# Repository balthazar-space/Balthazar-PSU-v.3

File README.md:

# Balthazar

Open-hardware laptop computer modules description and concept.

These are electronic schematic modules as presented at https://balthazar.space/wiki/Balthazar with the main aim for team access. See the [main repository](https://github.com/balthazar-space/balthazar) for other designs.

# Balthazar PSU v.3 

Module BalthazarPSU3 is a combined 1S battery charger, buck-boost converter to 5V, boost converter to 12V and stereo power amplifier. 

KiCad 6.99 files.

## License

All resources except the keyboard firmware - which is licensed with with GPLv3 or later - licensed under the CERN Open Hardware Licence CERN-OHL W V.2.0

Version 2.0 of the CERN-OHL introduces three variants of the licence – strongly (S) reciprocal, weakly (W) reciprocal and permissive (P) – which aim to address specific constraints caused by different collaboration models currently used in open-hardware projects. 

The first two variants mean that if any product is made using an open hardware design, the design of that product, including any improvements or modifications, should be made available under the same licence as that of the original product. Permissive licences do not impose this condition.

See the [LICENSE.md](./LICENSE.md) file for more information.

## Funding

This project is funded through the [NGI Zero Entrust Fund](https://nlnet.nl/entrust), a fund
established by [NLnet](https://nlnet.nl) with financial support from the European Commission's
[Next Generation Internet](https://ngi.eu) program. Learn more on the [NLnet project page](https://nlnet.nl/project/Balthazar-Casing/).

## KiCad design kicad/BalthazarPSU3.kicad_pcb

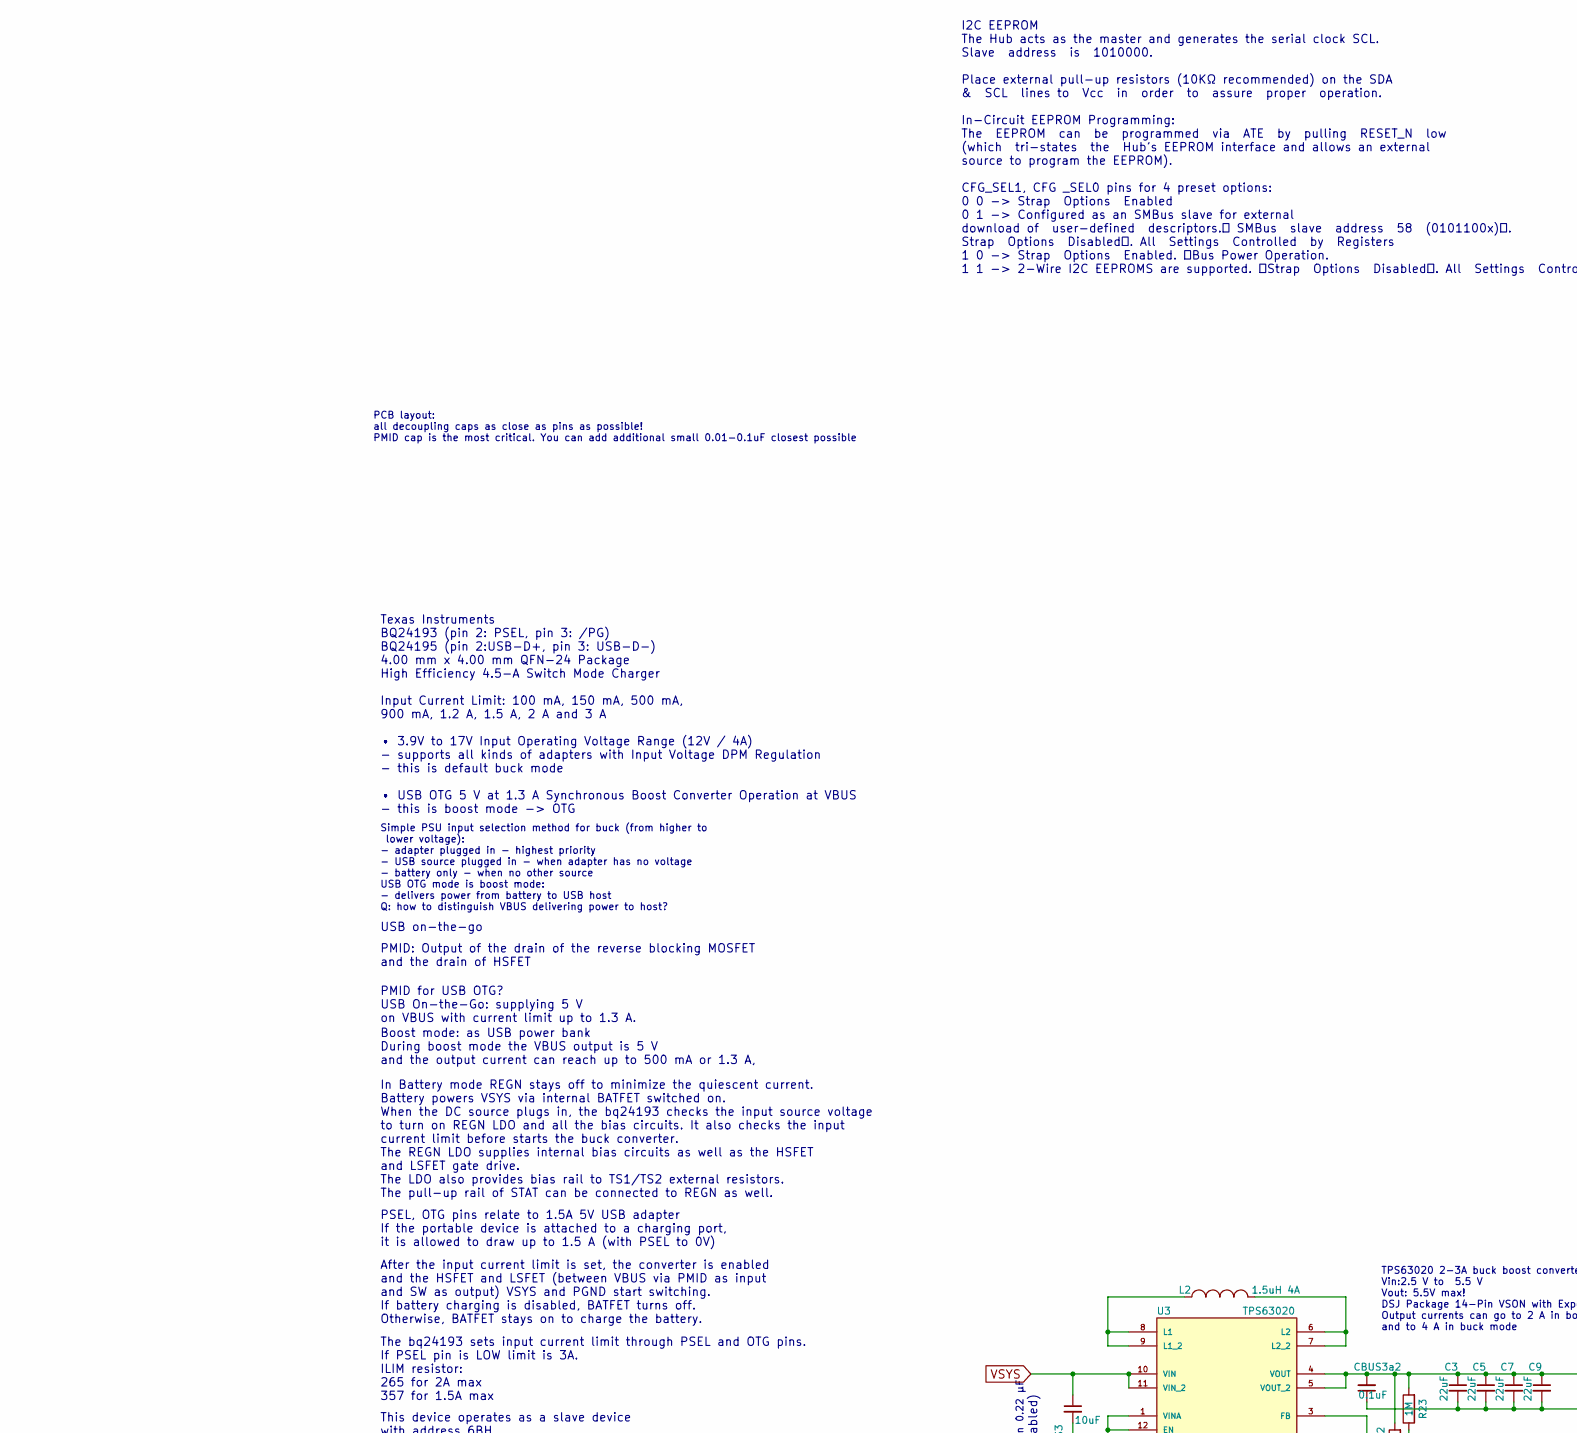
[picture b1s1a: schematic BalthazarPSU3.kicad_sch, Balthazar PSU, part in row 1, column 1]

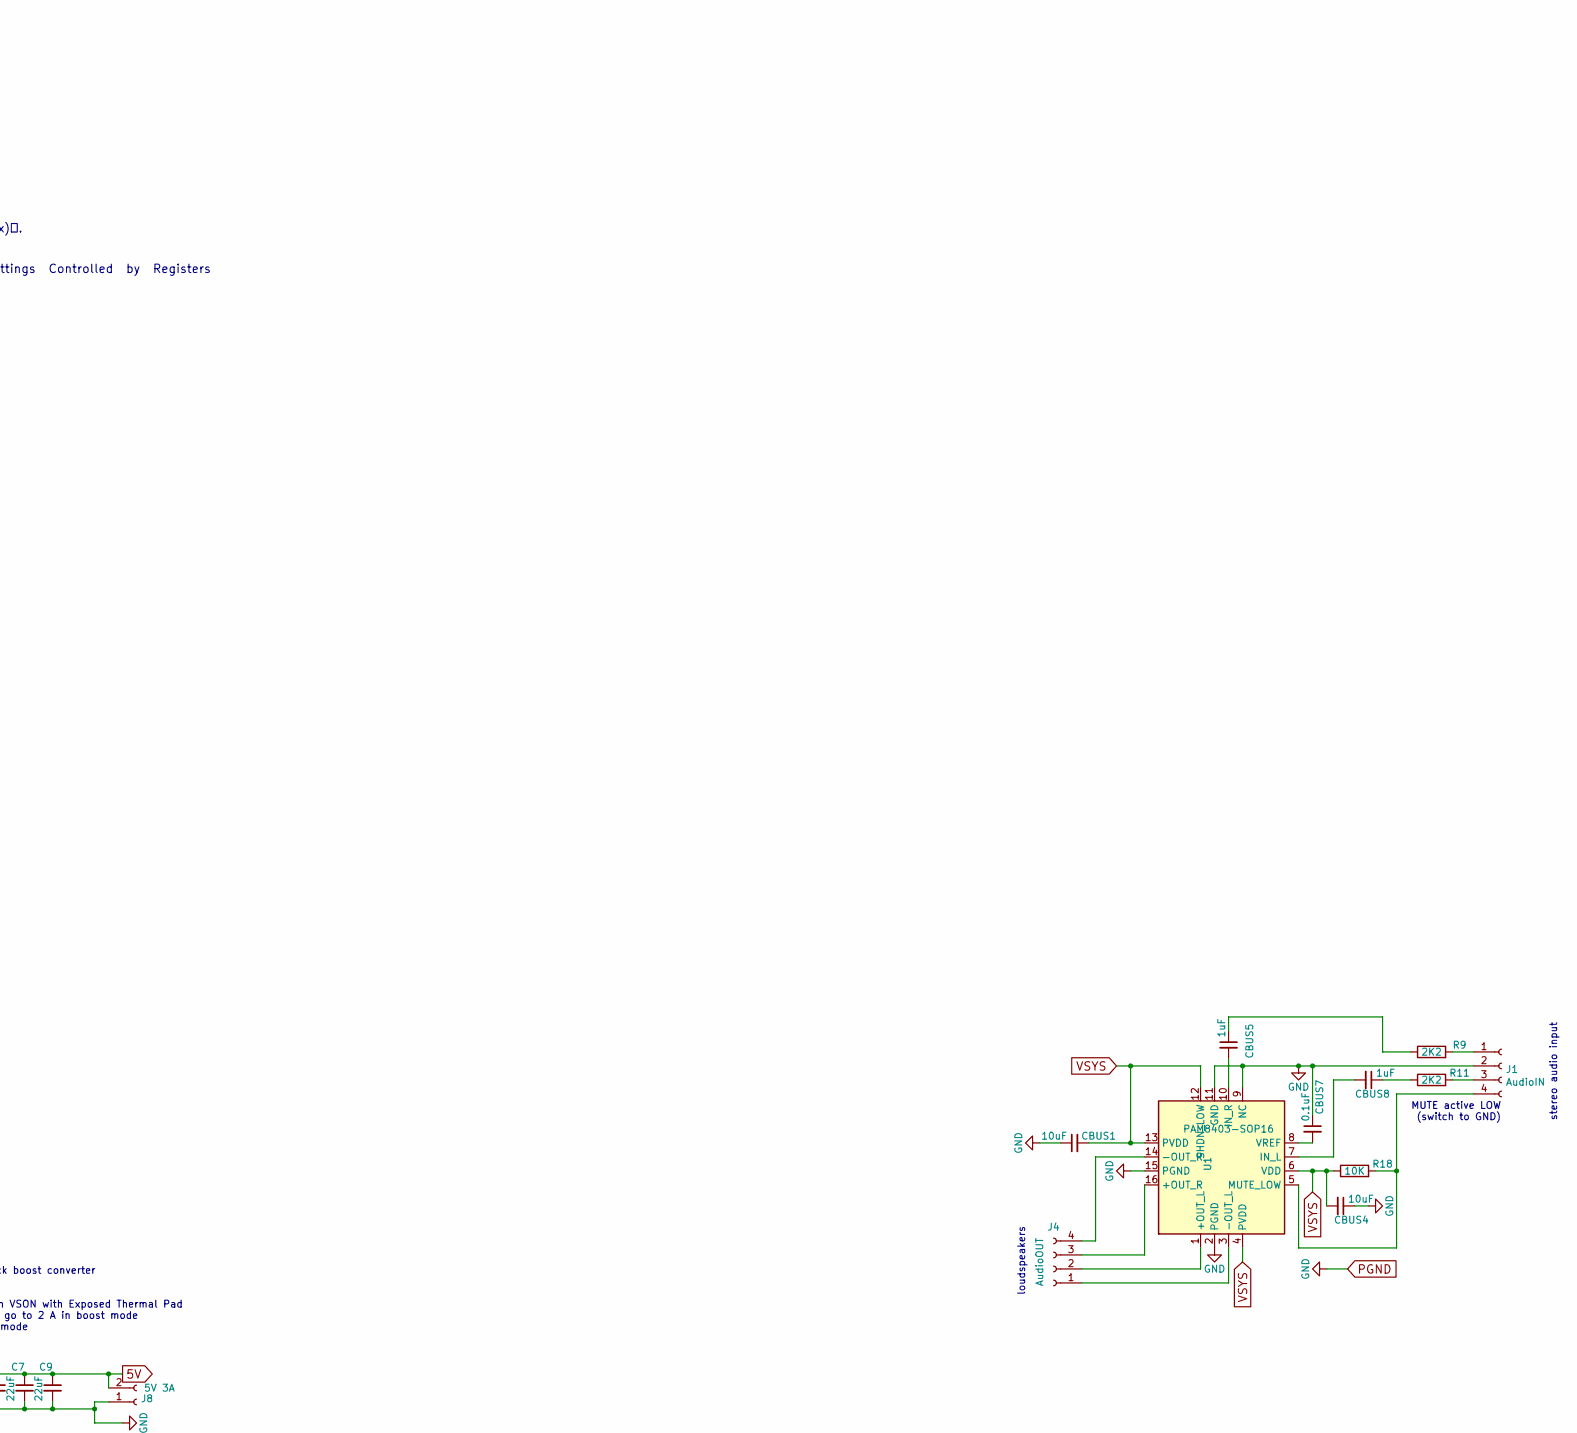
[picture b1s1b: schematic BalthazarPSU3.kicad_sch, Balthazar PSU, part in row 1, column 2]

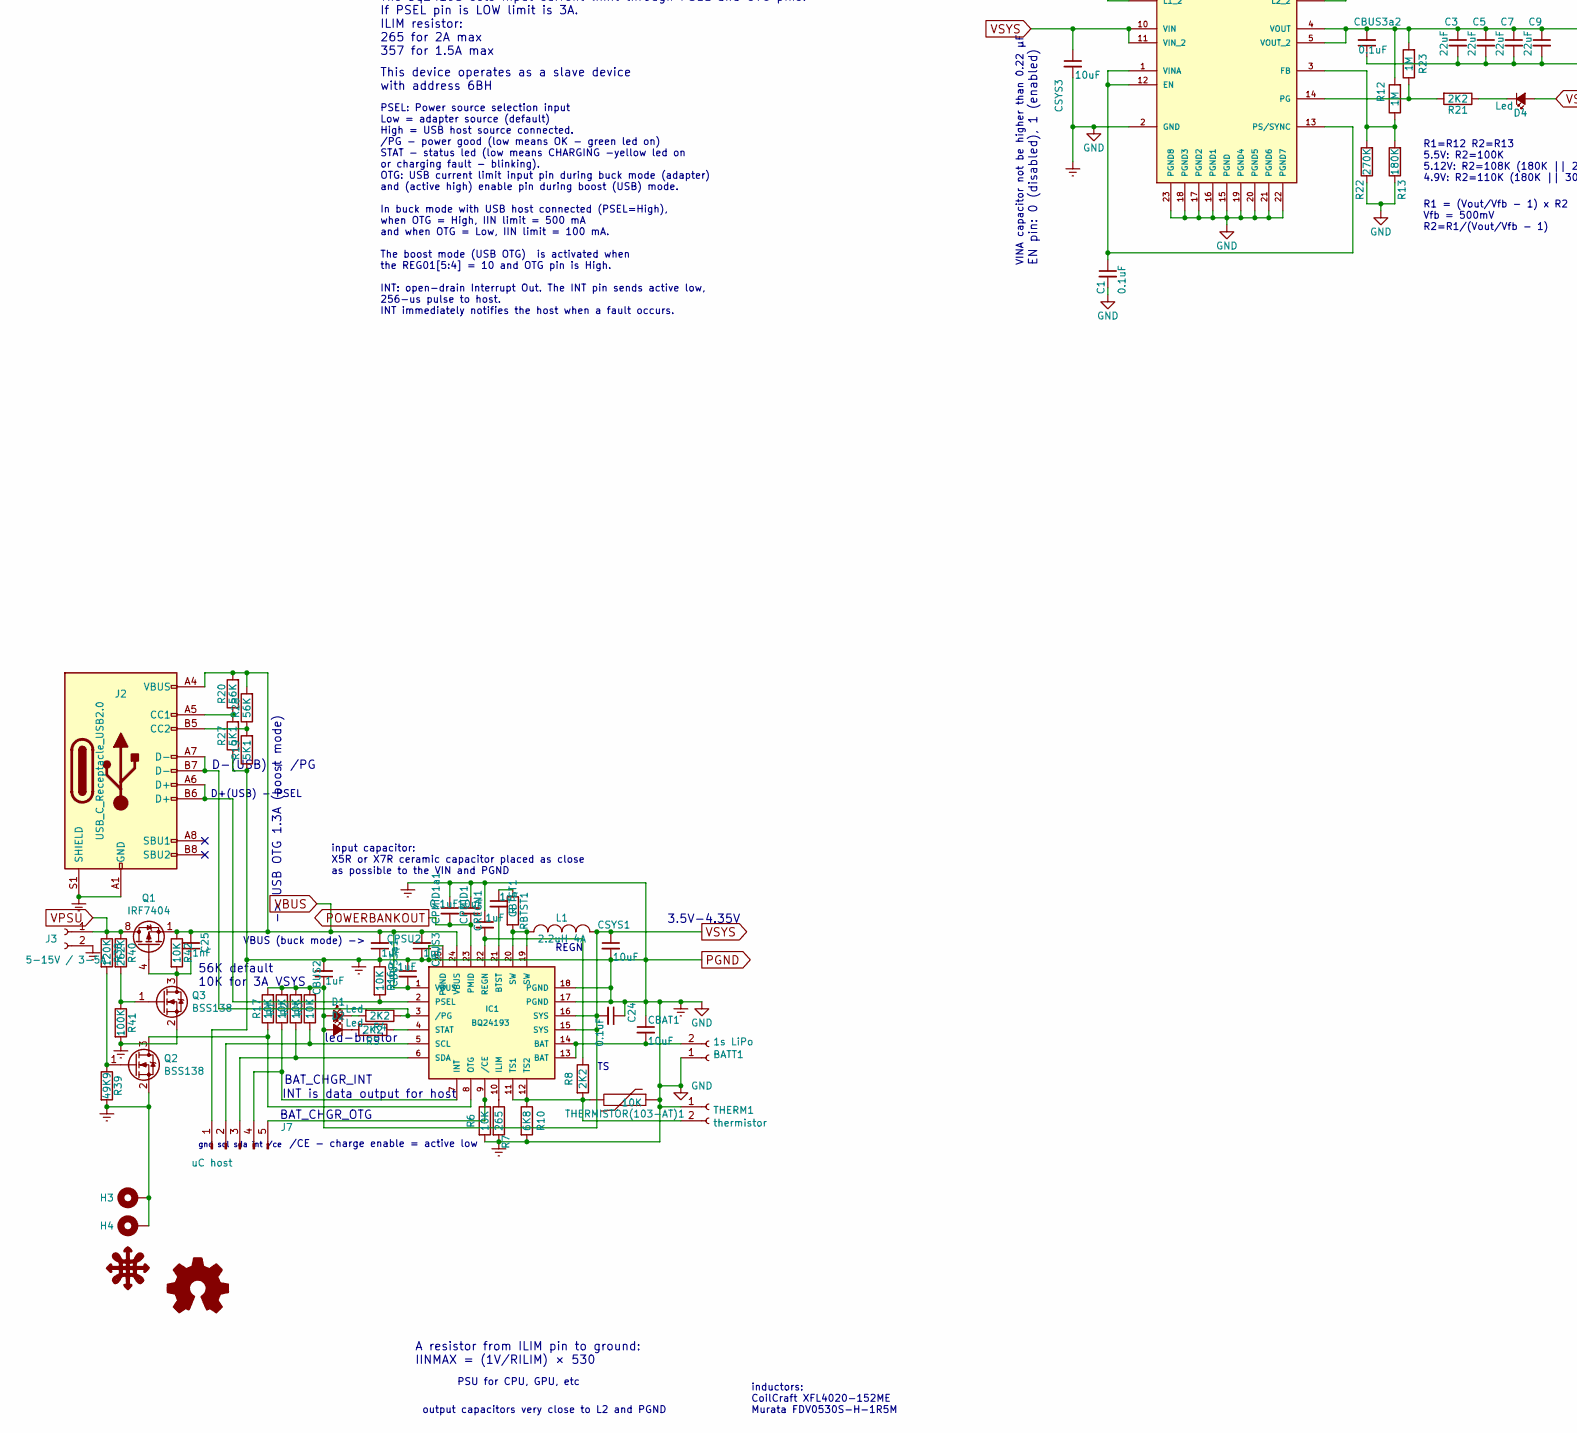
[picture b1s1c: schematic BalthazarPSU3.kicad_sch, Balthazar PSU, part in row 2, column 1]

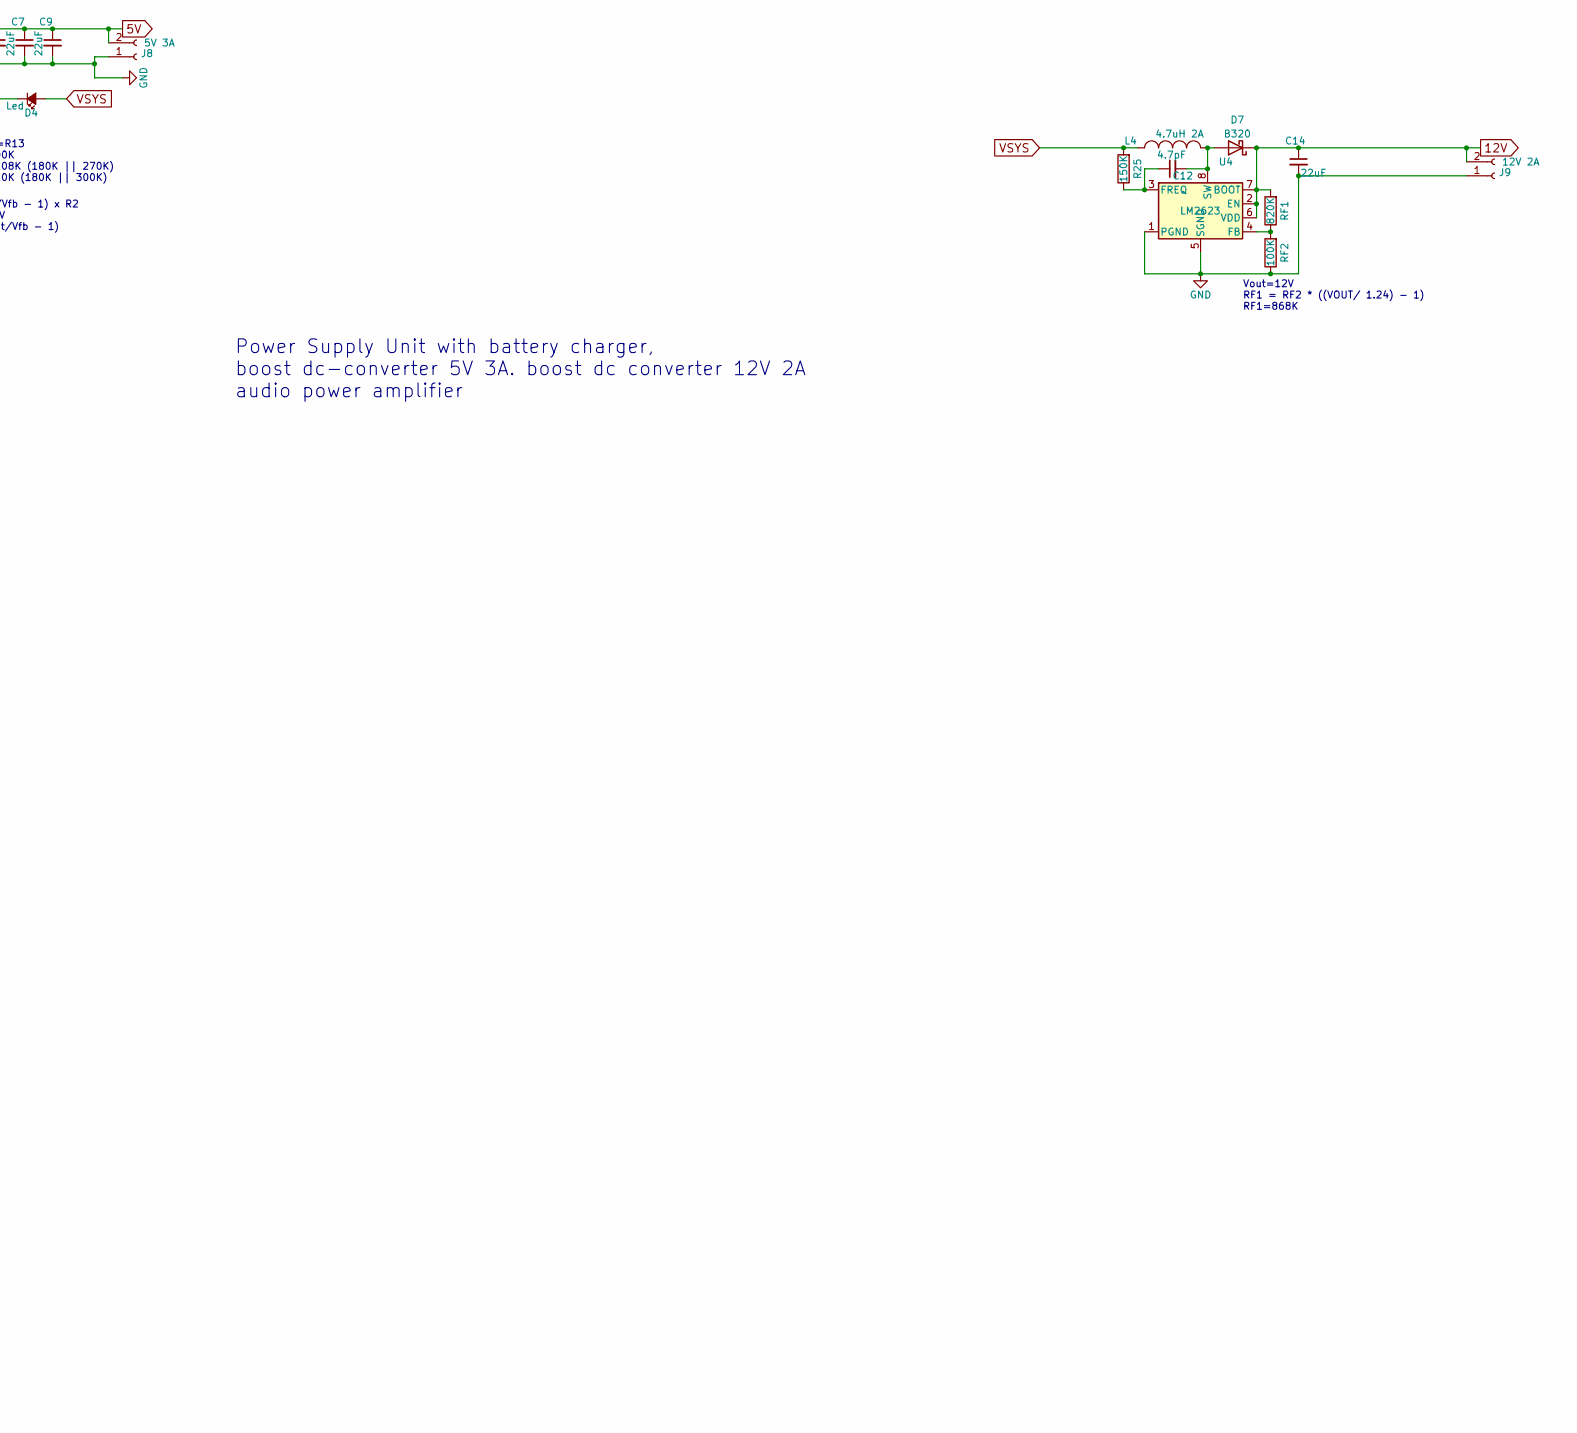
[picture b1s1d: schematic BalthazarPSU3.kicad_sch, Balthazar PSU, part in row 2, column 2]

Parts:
BATT1: 1s LiPo; TerminalBlock_bornier-2_P5.08mm
C1, C24: 0.1uF; C_0805_2012Metric
C3, C5, C7, C9, C14: 22uF; C_1206_3216Metric
C12: 4.7pF; C_0805_2012Metric
C25: 1nF; C_0805_2012Metric
CBAT1: 10uF; C_1206_3216Metric
CBTST1: 1uF; C_1206_3216Metric
CBUS1, CBUS4: 10uF; C_1206_3216Metric
CBUS2, CBUS3, CBUS5, CBUS8: 1uF; C_1206_3216Metric
CBUS3a1, CBUS3a2, CBUS7: 0.1uF; C_0805_2012Metric
CPMID1: 10uF; C_1206_3216Metric
CPMID1a1: 0.1uF; C_0805_2012Metric
CPSU2: 1uF; C_1206_3216Metric
CREGN1: 1uF; C_1206_3216Metric
CSYS1, CSYS3: 10uF; C_1206_3216Metric
D1, D2, D4: Led; LED_1206_3216Metric
D7: B320; D_SMB
H3: hole; MountingHole_2.2mm_M2_Pad
H4: MountingHole_Pad; MountingHole_2.2mm_M2_Pad
IC1: BQ24193; QFN-24-1EP_4x4mm_P0.5mm_EP2.7x2.7mm_ThermalVias
J1: AudioIN; PinSocket_1x04_P2.00mm_Vertical
J2: USB_C_Receptacle_USB2.0; USB_C_Receptacle_GCT_USB4085
J3: 5-15V / 3-5A; BarrelJack_Horizontal
J4: AudioOUT; PinSocket_1x04_P2.54mm_Vertical
J7: uC host; PinSocket_1x05_P2.00mm_Vertical
J8: 5V 3A; TerminalBlock_bornier-2_P5.08mm
J9: 12V 2A; TerminalBlock_bornier-2_P5.08mm
L1: 2.2uH 4A; L_Bourns_SRP7028A_7.3x6.6mm
L2: 1.5uH 4A; L_Bourns_SRP7028A_7.3x6.6mm
L4: 4.7uH 2A; L_Bourns_SRP5030T
Q1: IRF7404; SOIC-8_3.9x4.9mm_P1.27mm
Q2, Q3: BSS138; SOT-23
R1, R2, R3, R6, R16, R17, R18, R42: 10K; R_0805_2012Metric
R4, R5, R8, R9, R11, R21: 2K2; R_0805_2012Metric
R7: 265; R_0805_2012Metric
R10: 6K8; R_0805_2012Metric
R12, R23: 1M; R_0805_2012Metric
R13: 180K; R_0805_2012Metric
R19, R27: 5K1; R_0805_2012Metric
R20, R28: 56K; R_0805_2012Metric
R22: 270K; R_0805_2012Metric
R25: 150K; R_0805_2012Metric
R38: 120K; R_1206_3216Metric
R39: 49K9; R_1206_3216Metric
R40: 262K; R_0805_2012Metric
R41: 100K; R_0805_2012Metric
RBTST1: R; R_0805_2012Metric
RF1: 820K; R_0805_2012Metric
RF2: 100K; R_0805_2012Metric
THERM1: thermistor; TestPoint_2Pads_Pitch2.54mm_Drill0.8mm
THERMISTOR(103-AT)1: 10K; R_0805_2012Metric
U1: PAM8403-SOP16; SOP-16_4.4x10.4mm_P1.27mm
U3: TPS63020; QFN14-3X4MM
U4: LM2623; VSSOP-8_3.0x3.0mm_P0.65mm

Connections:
5V: C3.1, C5.1, C7.1, C9.1, CBUS3a2.2, J8.2, R12.2, R23.2, U3.4 (VOUT), U3.5 (VOUT_2)
12V: C14.1, D7.1 (K), J9.2, RF1.2, U4.2 (EN), U4.6 (VDD), U4.7 (BOOT)
unnamed: BATT1.2, CBAT1.2, IC1.13 (BAT), IC1.14 (BAT)
unnamed: CBTST1.1, RBTST1.1
unnamed: CBUS5.1, R9.1
unnamed: CBUS8.1, R11.1
unnamed: D1.2 (C), R4.2
unnamed: D2.2 (C), R5.2
unnamed: D4.2 (C), R21.1
unnamed: C12.2, D7.2 (A), L4.2, U4.8 (SW)
unnamed: CBTST1.2, IC1.21 (BTST)
unnamed: IC1.10 (ILIM), R7.1
unnamed: IC1.7 (INT), J7.4, R1.1
unnamed: IC1.8 (OTG), Q2.3 (D), R17.1
unnamed: IC1.2 (PSEL), J2.A6 (D+), J2.B6 (D+), R16.2
unnamed: CREGN1.2, IC1.22 (REGN), R8.1
unnamed: IC1.5 (SCL), J7.2, R3.1
unnamed: IC1.6 (SDA), J7.3, R2.1
unnamed: IC1.4 (STAT), R5.1
unnamed: IC1.19 (SW), IC1.20 (SW), L1.1, RBTST1.2
unnamed: IC1.11 (TS1), IC1.12 (TS2), R8.2, R10.1, THERM1.2, THERMISTOR(103-AT)1.2
unnamed: IC1.9 (/CE), J7.5, R6.1
unnamed: IC1.3 (/PG), J2.A7 (D-), J2.B7 (D-), R4.1
unnamed: J1.1, R9.2
unnamed: J1.3, R11.2
unnamed: J1.4, R18.2, U1.5 (MUTE_LOW)
unnamed: J2.A5 (CC1), R20.1, R27.2
unnamed: J2.B5 (CC2), R19.2, R28.1
unnamed: J4.1, U1.3 (-OUT_L)
unnamed: J4.2, U1.1 (+OUT_L)
unnamed: J4.3, U1.16 (+OUT_R)
unnamed: J4.4, U1.14 (-OUT_R)
unnamed: C25.1, Q1.4 (G), Q3.3 (D), R42.2
unnamed: Q2.1 (G), R38.2, R39.1
unnamed: Q3.1 (G), R40.2, R41.1
unnamed: CBUS8.2, U1.7 (IN_L)
unnamed: CBUS5.2, U1.10 (IN_R)
unnamed: CBUS7.2, U1.8 (VREF)
unnamed: C1.1, U3.1 (VINA), U3.12 (EN), U3.13 (PS/SYNC)
unnamed: R12.1, R13.2, R22.2, U3.3 (FB)
unnamed: L2.1, U3.8 (L1), U3.9 (L1_2)
unnamed: L2.2, U3.6 (L2), U3.7 (L2_2)
unnamed: R21.2, R23.1, U3.14 (PG)
unnamed: RF1.1, RF2.2, U4.4 (FB)
unnamed: C12.1, R25.1, U4.3 (FREQ)
PGND: BATT1.1, C1.2, C3.2, C5.2, C7.2, C9.2, C14.2, C24.1, CBAT1.1, CBUS1.1, CBUS2.2, CBUS3.1, CBUS3a1.1, CBUS3a2.1, CBUS4.1, CBUS7.1, CPMID1.1, CPMID1a1.1, CPSU2.1, CREGN1.1, CSYS1.2, CSYS3.2, H3.1, H4.1, IC1.17 (PGND), IC1.18 (PGND), IC1.25 (PGND), J1.2, J2.A1 (GND), J2.A12 (GND), J2.B1 (GND), J2.B12 (GND), J2.S1 (SHIELD), J3.2, J7.1, J8.1, J9.1, Q2.2 (S), Q3.2 (S), R6.2, R7.2, R10.2, R13.1, R16.1, R19.1, R22.1, R27.1, R39.2, R41.2, RF2.1, THERM1.1, THERMISTOR(103-AT)1.1, U1.2 (PGND), U1.9 (NC), U1.11 (GND), U1.15 (PGND), U3.2 (GND), U3.15 (PGND), U3.16 (PGND1), U3.17 (PGND2), U3.18 (PGND3), U3.19 (PGND4), U3.20 (PGND5), U3.21 (PGND6), U3.22 (PGND7), U3.23 (PGND8), U4.1 (PGND), U4.5 (SGND)
POWERBANKOUT: CPMID1.2, CPMID1a1.2, IC1.23 (PMID)
VBUS: C25.2, CBUS3.2, CBUS3a1.2, CPSU2.2, IC1.1 (VBUS), IC1.24 (VBUS), J2.A4 (VBUS), J2.A9 (VBUS), J2.B4 (VBUS), J2.B9 (VBUS), Q1.1 (S), Q1.2 (S), Q1.3 (S), R20.2, R28.2, R42.1
VPSU: J3.1, Q1.5 (D), Q1.6 (D), Q1.7 (D), Q1.8 (D), R38.1, R40.1
VSYS: C24.2, CBUS1.2, CBUS2.1, CBUS4.2, CSYS1.1, CSYS3.1, D1.1 (A), D2.1 (A), D4.1 (A), IC1.15 (SYS), IC1.16 (SYS), L1.2, L4.1, R1.2, R2.2, R3.2, R17.2, R18.1, R25.2, U1.4 (PVDD), U1.6 (VDD), U1.12 (SHDN_LOW), U1.13 (PVDD), U3.10 (VIN), U3.11 (VIN_2)

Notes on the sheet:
PSEL: Power source selection input Low = adapter source (default) High = USB host source connected. /PG - power good (low means OK - green led on) STAT - status led (low means CHARGING -yellow led on or charging fault - blinking). OTG: USB current limit input pin during buck mode (adapter) and (act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
output capacitors very close to L2 and PGND
REGN
PCB layout: all decoupling caps as close as pins as possible! PMID cap is the most critical. You can add additional small 0.01-0.1uF closest possible
3.5V-4.35V
56K default 10K for 3A
Texas Instruments BQ24193 (pin 2: PSEL, pin 3: /PG) BQ24195 (pin 2:USB-D+, pin 3: USB-D-) 4.00 mm x 4.00 mm QFN-24 Package High Efficiency 4.5-A Switch Mode Charger Input Current Limit: 100 mA, 150 mA, 500 mA, 900 mA, 1.2 A, 1.5 A, 2 A and 3 A • 3.9V to 17V Input Operating Voltage Range (12V / 4A) 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
PMID for USB OTG? USB On-the-Go: supplying 5 V on VBUS with current limit up to 1.3 A.
gnd scl sda int /ce
VBUS (buck mode) ->
D+(USB) - PSEL
stereo audio input
This device operates as a slave device with address 6BH
PMID: Output of the drain of the reverse blocking MOSFET and the drain of HSFET
In Battery mode REGN stays off to minimize the quiescent current. Battery powers VSYS via internal BATFET switched on. When the DC source plugs in, the bq24193 checks the input source voltage to turn on REGN LDO and all the bias circuits. It also checks the input current limit before starts the buc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
Vout=12V RF1 = RF2 * ((VOUT/ 1.24) − 1) RF1=868K
R1 = (Vout/Vfb - 1) x R2 Vfb = 500mV R2=R1/(Vout/Vfb - 1)
Boost mode: as USB power bank During boost mode the VBUS output is 5 V and the output current can reach up to 500 mA or 1.3 A,
-> USB OTG 1.3A (boost mode)
INT is data output for host
BAT_CHGR_OTG
The bq24193 sets input current limit through PSEL and OTG pins. If PSEL pin is LOW limit is 3A. ILIM resistor: 265 for 2A max 357 for 1.5A max
/CE - charge enable = active low
USB on-the-go
I2C EEPROM The Hub acts as the master and generates the serial clock SCL. Slave address is 1010000. Place external pull-up resistors (10KΩ recommended) on the SDA & SCL lines to Vcc in order to assure proper operation. In-Circuit EEPROM Programming: The EEPROM can be programmed via ATE by pulling R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
input capacitor: X5R or X7R ceramic capacitor placed as close as possible to the VIN and PGND
PSEL, OTG pins relate to 1.5A 5V USB adapter If the portable device is attached to a charging port, it is allowed to draw up to 1.5 A (with PSEL to 0V)
D-(USB) - /PG
Power Supply Unit with battery charger, boost dc-converter 5V 3A. boost dc converter 12V 2A audio power amplifier
VINA capacitor not be higher than 0.22 μF
TPS63020 2-3A buck boost converter Vin:2.5 V to 5.5 V Vout: 5.5V max! DSJ Package 14-Pin VSON with Exposed Thermal Pad Output currents can go to 2 A in boost mode and to 4 A in buck mode
MUTE active LOW (switch to GND)
R1=R12 R2=R13 5.5V: R2=100K 5.12V: R2=108K (180K || 270K) 4.9V: R2=110K (180K || 300K)
After the input current limit is set, the converter is enabled and the HSFET and LSFET (between VBUS via PMID as input and SW as output) VSYS and PGND start switching. If battery charging is disabled, BATFET turns off. Otherwise, BATFET stays on to charge the battery.
led-bicolor
A resistor from ILIM pin to ground: IINMAX = (1V/RILIM) × 530
PSU for CPU, GPU, etc
EN pin: 0 (disabled), 1 (enabled)
loudspeakers
VSYS

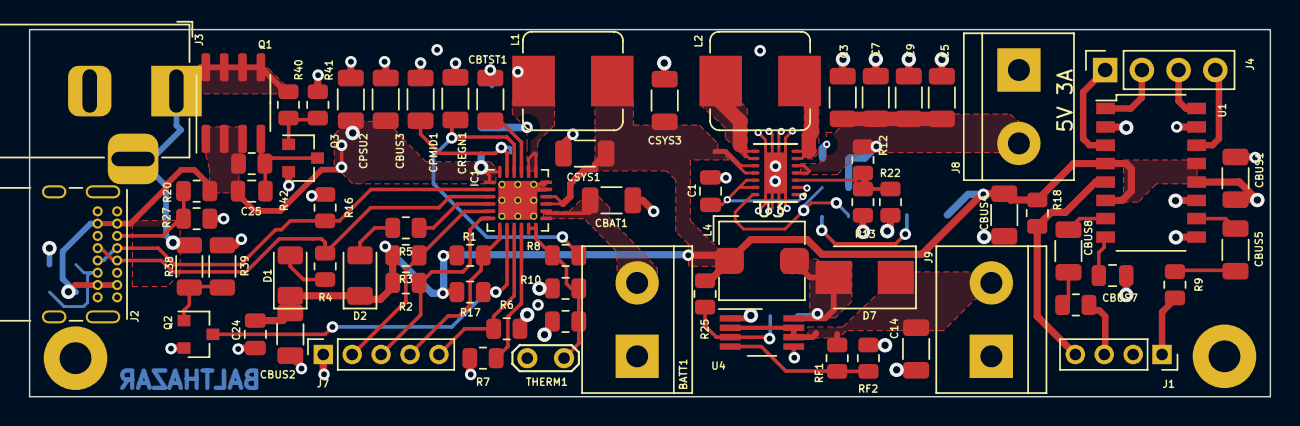
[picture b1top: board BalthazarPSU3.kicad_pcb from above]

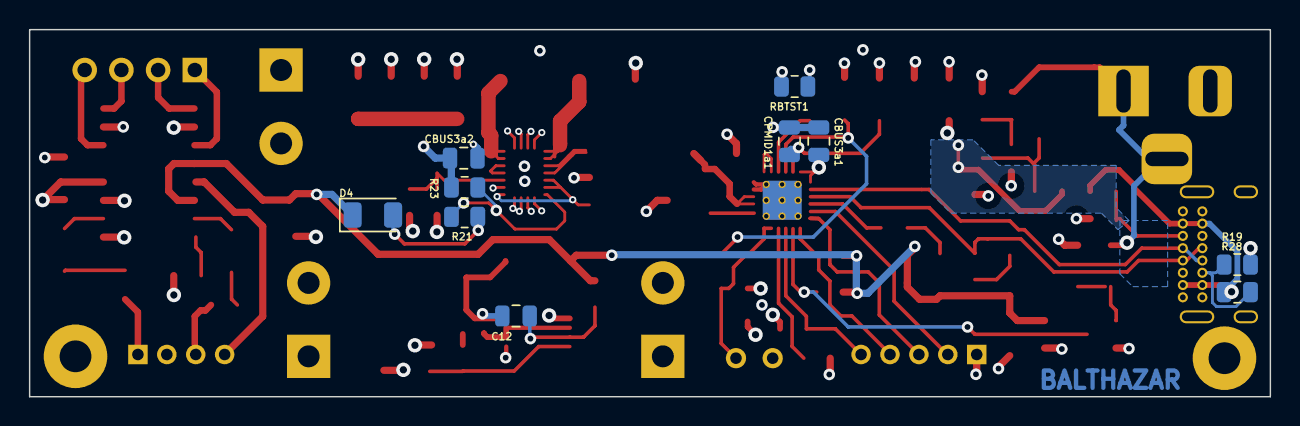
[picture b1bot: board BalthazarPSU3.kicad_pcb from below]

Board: 4 copper layers, 85.9 x 25.4 mm, 84 parts (10 on the bottom side), 50 nets.

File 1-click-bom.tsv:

References,Qty,Description,Manufacturer,MPN,Manufacturer,MPN,Manufacturer,MPN,Manufacturer,MPN,Digikey,Mouser,RS,Newark,Farnell,LCSC,JLC Assembly
"C1, C24, CBUS3a1, CBUS3a2, CBUS7, CPMID1a1",6,0.1uF C_0805_2012Metric,KEMET,C0402C104K4RACTU,Yageo,CC0805KRX7R9BB104,Murata,GRM21BR71H104KA01L,,,311-1140-6-ND,80C0402C104K4R,8015145P,,1288252,,
"C3, C5, C7, C9, C14",5,22uF C_1206_3216Metric,AVX,12066C226KAT2A,Taiyo Yuden,EMK316ABJ226ML-T,,,,,587-3328-6-ND,963EMK316ABJ226MLT,1356734,,1657942,,
C12,1,4.7pF C_0805_2012Metric,KEMET,C0805C479C5GACTU,KEMET,C0805C479D5GACTU,,,,,399-C0805C479D5GAC7800DKR-ND,80C0805C479D5G,1464340P,,1800809,,
C25,1,1nF C_0805_2012Metric,KEMET,C0805C102J1GACTU,KEMET,C0805C102K5RACTU,,,,,399-C0805C102K5RAC7800DKR-ND,80C0805C102K5R,8029958P,,1414660,,
"R1, R2, R3, R6, R16, R17, R18, R42",8,10K R_0805_2012Metric,Panasonic,ERJ-3EKF1002V,Panasonic,ERJ-6ENF1002V,TE Connectivity,CPF0805B10KE,Panasonic,ERJ-6GEYJ103V,P10.0KHCT-ND,667ERJ6ENF1002V,6662594,,2303192,,
"R4, R5, R8, R9, R11, R21",6,2K2 R_0805_2012Metric,Panasonic,ERJ-2RKF2201X,Panasonic,ERJ-3GEYJ222V,TE Connectivity,CRG0805F2K2,Panasonic,ERJP06F2201V,P2.2KGCT-ND,667ERJ2RKF2201X,7217775P,,1750759,,
"R12, R23",2,1M R_0805_2012Metric,Panasonic,ERJ-3GEYJ105V,Panasonic,ERJ-6GEYJ105V,,,,,P1.0MGCT-ND,667ERJ3GEYJ105V,7326536,,2057738,,
"R19, R27",2,5K1 R_0805_2012Metric,Panasonic,ERJ-6ENF5101V,Yageo,RC0805FR-075K1L,,,,,311-5.10KCRDKR-ND,667ERJ6ENF5101V,1995733P,,3496074,,
"R20, R28",2,56K 0805_2012Metric,Yageo,RMCF0805JT56K0,Yageo,AC0805FR-0756KL,Yageo,RC0805FR-0756KL,,,311-56.0KCRCT-ND,603RC0805FR0756KL,1995730,,9237844,,
R7,1,270R 0805_2012Metric,TE Connectivity,3520270RJT,TE Connectivity,CRG0805F270R,Panasonic,ERJ-6GEYJ271V,,,A126355CT-ND,667ERJ6GEYJ271V,2240339,,3399601,,
R10,1,6K8 0805_2012Metric,Yageo,RC0805FR-076K8L,Yageo,AC0805FR-076K8L,,,,,311-6.80KCRCT-ND,603AC0805FR076K8L,1995745,,9237739RL,,
R13,1,180K R_0805_2012Metric,Yageo,RC0805JR-07180KL,Bourns,CR0805-JW-184ELF,,,,,311-180KARCT-ND,603RC0805JR07180KL,,,9234284,,
R22,1,270K R_0805_2012Metric,,RC0805JR-07270KL,Yageo,RC0805JR-07270KL,,,,,311-270KARDKR-ND,603RC0805JR07270KL,,,9234306,,
R25,1,150K R_0805_2012Metric,,RC0805JR-07150KL,Yageo,RC0805JR-07150KL,,,,,311-150KARDKR-ND,603RC0805JR07150KL,,,9234276,,
R38,1,120K R_1206_3216Metric,,AC1206JR-07150KL,Yageo,AC1206JR-07150KL,,,,,YAG3920CT-ND,603AC1206JR07150KL,,,,,
R39,1,49K9 R_1206_3216Metric,,RC1206FR-0749K9L,Yageo,RC1206FR-0749K9L,,,,,311-49.9KFRCT-ND,603RC1206FR0749K9L,,,3951060RL,,
R40,1,270K R_0805_2012Metric,,RC0805JR-07270KL,Yageo,RC0805JR-07270KL,,,,,311-270KARDKR-ND,603RC0805JR07270KL,,,9234306,,
R41,1,100K R_0805_2012Metric,,RC0805FR-13100KL,Yageo,RC0805FR-13100KL,,,,,13-RC0805FR-13100KLDKR-ND,603RC0805FR13100KL,,,3951189RL,,
L1,1,2.2uH SRP7028A,Bourns,SRP7028A-2R2M,,,,,,,SRP7028A-2R2MCT-ND,652SRP7028A2R2M,,,2434097,,
L2,1,1.5uH SRP7028A,Bourns,SRP7028A-1R5M,,,,,,,SRP7028A-1R5MCT-ND,652SRP7028A1R5M,2231849P,,2434095,,
L4,1,4.7uH SRP5030T,Bourns,SRP5030T-4R7M,,,,,,,SRP5030T-4R7MDKR-ND,652SRP5030T4R7M,7763985P,,2309887,,
"D1, D2, D4",3,Led LED_1206_3216Metric,,RPG1102W-660-TR,Stanley Electric,RPG1102W-660-TR,,,,,404-1232-1-ND,327RPG1102W660TR,,,,,
D7,1,B320,Bourns,CD214B-B320R,Diodes Inc.,B320B-13-F,Diodes Inc.,B330-13-F,,,B320B-FDICT-ND,652CD214BB320R,7513269,,3944811RL,,
U1,1,PAM8403,Diodes Inc.,PAM8403DR-H,Diodes Inc.,PAM8403DR,,,,,PAM8403DR-HDICT-ND,621PAM8403DRH,7902975P,,3373823,,
U2,1,TPS63020,Texas Instruments,TPS63020DSJT,,,,,,,296-27230-2-ND,595TPS63020DSJT,8123808,,3007458,,
U4,1,LM2623,Texas Instruments,LM2623AMM/NOPB,Texas Instruments,LM2623MM/NOPB,,,,,LM2623AMM/NOPBCT-ND,926LM2623AMM/NOPB,5333901,,3121524RL,,
"CBTST1, CBUS2, CBUS3, CBUS5, CBUS8, CPSU2, CREGN1",7,1uF C_1206_3216Metric,KEMET,C1206C105K3RACTU,,,,,,,399-C1206C105K3RAC7800DKR-ND,80C1206C105K3R,4348110P,,9227865,,
"CBAT1, CBUS1, CBUS4, CPMID1, CSYS1, CSYS3",6,10uF C_1206_3216Metric,KEMET,T491A106M016AT,,,,,,,399-3687-6-ND,80T491A106M016,8015454P,,1650980,,
"Q2, Q3",2,BSS138,Nexperia,"BSS138P,215",Nexperia,"BSS138BK,215",ROHM,BSS138BKT116,,,846-BSS138BKT116CT-ND,771BSS138P215,7920891P,,2053833,,
BATT1,1,1s LiPo TerminalBlock_bornier-2_P5.08mm,,,,,,,,,,,,,,,
IC1,1,BQ24193,Texas Instruments,BQ24193RGER,,,,,,,296-35046-2-ND,595BQ24193RGER,,,,,
Q1,1,IRF7404,Infineon,IRF7404TRPBF,,,,,,,IRF7404PBFCT-ND,942IRF7404TRPBF,1781525,,2468018,,
RBTST1,1,R R_0805_2012Metric,,,,,,,,,,,,,,,
RF1,1,820K R_0805_2012Metric,TE Connectivity,CRGP0805F820K,Panasonic,ERA6AEB824V,,,,,A130512DKR-ND,279CRGP0805F820K,566418P,,2861130,,
RF2,1,100K R_0805_2012Metric,Panasonic,ERJ-6ENF1003V,TE Connectivity,CPF0805B100KE,,,,,P100KCDKR-ND,667ERJ6ENF1003V,6662673P,,2303757,,
THERM1,1,thermistor TestPoint_2Pads_Pitch2.54mm_Drill0.8mm,,,,,,,,,,,,,,,
THERMISTOR(103-AT)1,1,10K R_0805_2012Metric,Panasonic,ERJ-6ENF1002V,TE Connectivity,CPF0805B10KE,,,,,A106043CT-ND,667ERJ6ENF1002V,6662594,,2303654,,
J1,1,AudioIN PinSocket_1x04_P2.00mm_Vertical,,,,,,,,,,,,,,,
J2,1,USB_C_Receptacle_USB2.0 USB_C_Receptacle_GCT_USB4085,,,,,,,,,,,,,,,
J3,1,5-15V / 3-5A BarrelJack_Horizontal,,,,,,,,,,,,,,,
J4,1,AudioOUT PinSocket_1x04_P2.54mm_Vertical,,,,,,,,,,,,,,,
J7,1,uC host PinSocket_1x05_P2.00mm_Vertical,,,,,,,,,,,,,,,
J8,1,5V 3A TerminalBlock_bornier-2_P5.08mm,,,,,,,,,,,,,,,
J9,1,12V 2A TerminalBlock_bornier-2_P5.08mm,,,,,,,,,,,,,,,

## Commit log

2022-06-08 Adding interactive BOM
2022-06-28 Sorting files
2022-06-29 Update 1-click_BOM
2022-07-10 Updating parts
2022-10-08 Adding new symbol and footprint for U2
2022-10-11 Switching to 4 layer board fix #10
2022-10-11 Adding info fix #9
2022-10-11 Removing all routed signal loops
2022-10-11 Routing all signals fix #11 fix #7
2022-10-11 For cleanup we need more space - switching schematics page to A3 #5
2022-10-11 MAking silkscreen text smaller #13
2022-10-11 Moving Silkscreen text fix #13
2022-10-11 fixing/checking design errors fix #12
2022-10-11 Improving schematics #5
2022-10-11 Moving USB lines
2022-10-11 Moving more lines
2022-10-12 More line moves
2022-10-12 More line moves fix #5
2022-10-12 Adding production files fix #8
2022-10-12 Adding pictures to readme

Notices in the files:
kicad/BalthazarPSU3.kicad_pcb:
License: CERN-OHL-S
